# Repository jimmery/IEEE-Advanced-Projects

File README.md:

# IEEE-Advanced-Projects
Labs and Code for UCLA IEEE Advanced Projects.

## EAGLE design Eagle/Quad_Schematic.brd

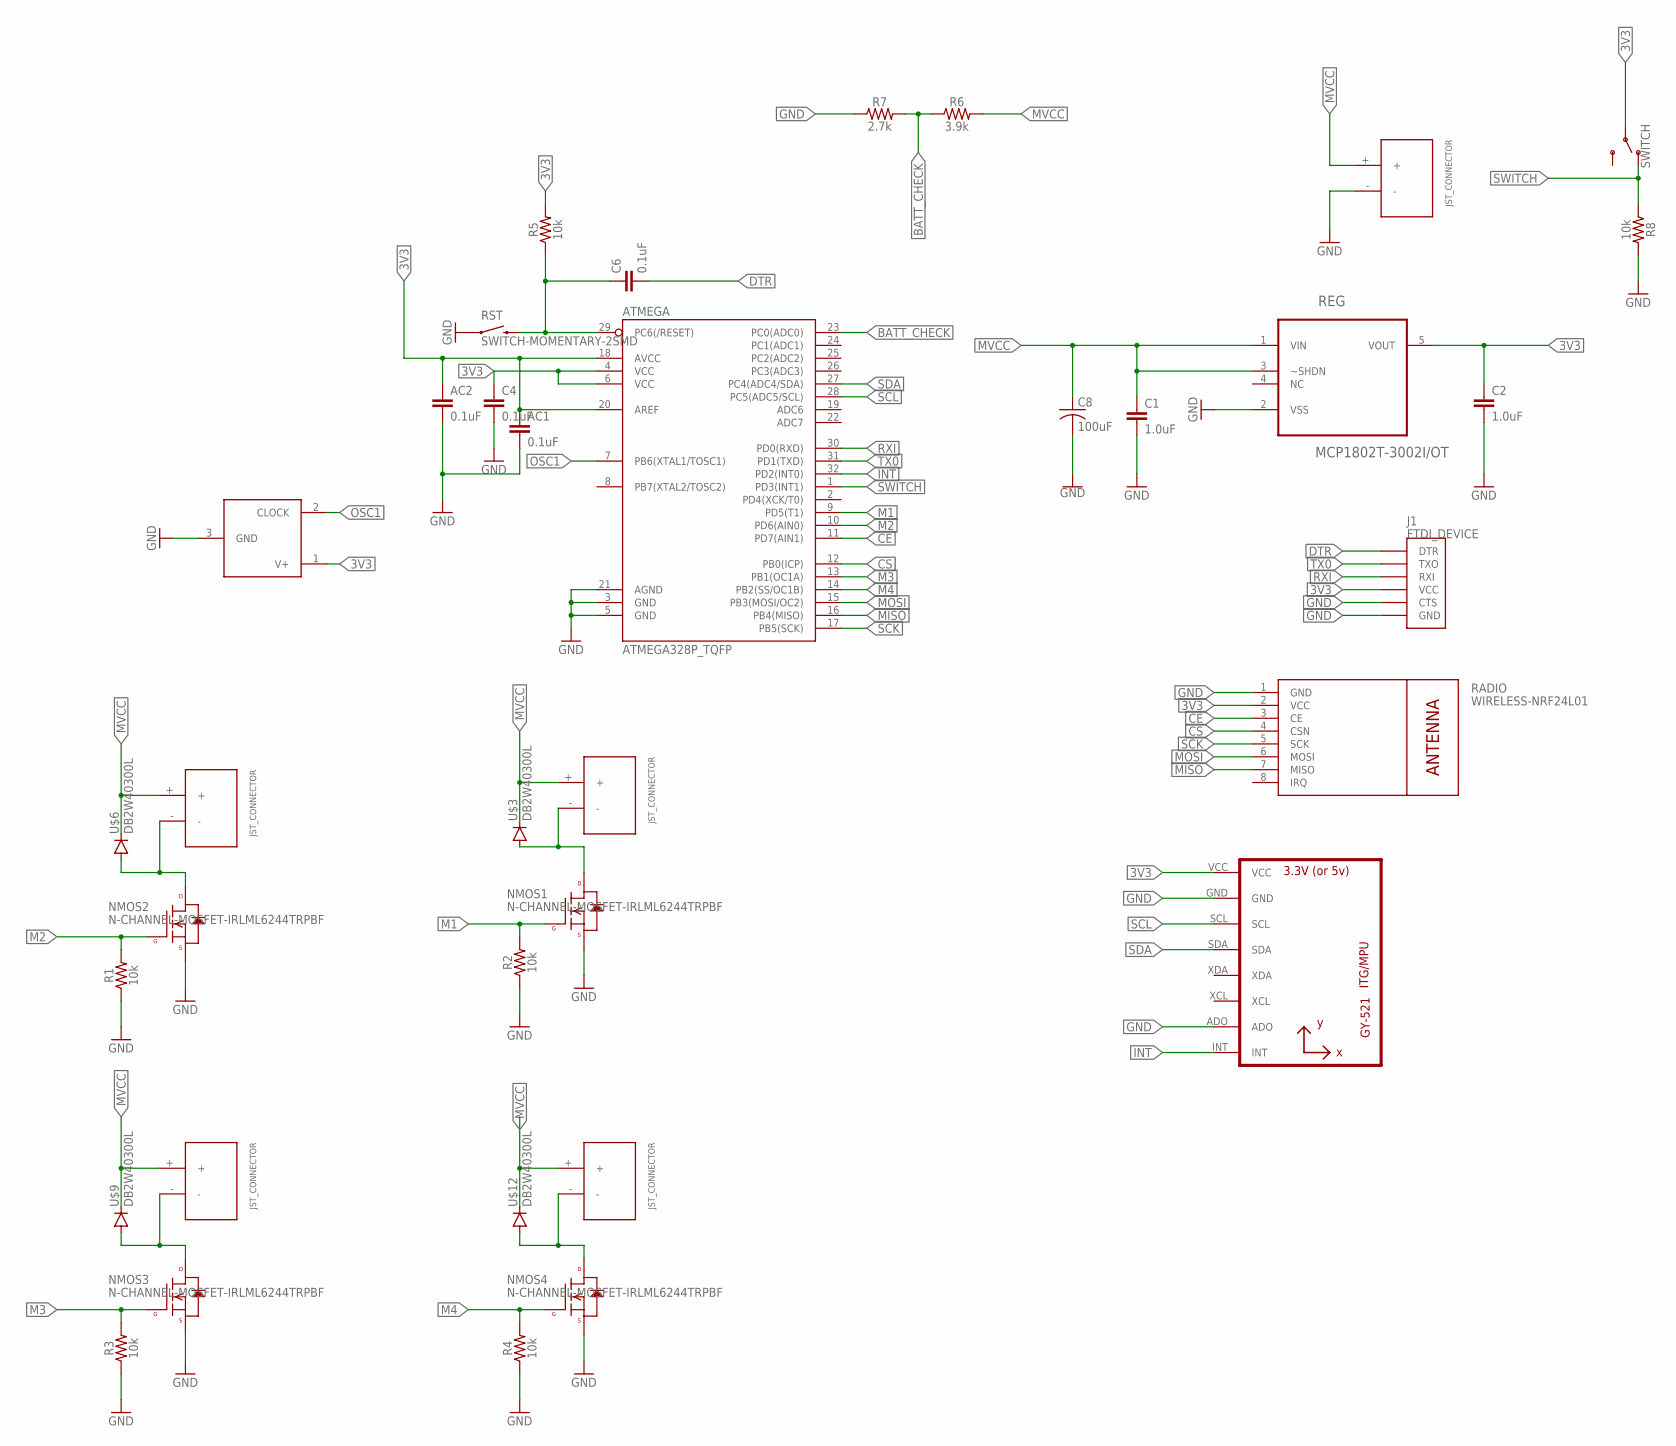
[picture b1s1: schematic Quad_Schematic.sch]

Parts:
AC1, AC2: 0.1uF; 0603
ATMEGA: ATMEGA328P_TQFP; TQFP32-08
BATT: JST_CONNECTOR_FEMALE
C1, C2: 1.0uF; 0603
C4, C6: 0.1uF; 0603
C8: 100uF; C1210
J1: FTDI_DEVICE; FTDI_DEVICE_SIDE
NMOS1, NMOS2, NMOS3, NMOS4: N-CHANNEL-MOSFET-IRLML6244TRPBF; SOT23-3
OSC: MAX7375; SC70-3L
R1, R2, R3, R4, R5, R8: 10k; 0603
R6: 3.9k; 0603
R7: 2.7k; 0603
RADIO: WIRELESS-NRF24L01
REG: MCP1802T-3002I/OT; SOT95P270X145-5N
RST: SWITCH-MOMENTARY-2SMD; TACTILE-SWITCH-SMD
SWITCH: SWITCH-SPDT-PTH-11.6X4.0MM; SWITCH_SPDT_PTH_11.6X4.0MM
U2: GY-521MPU6050; GY-521
U$2, U$5, U$8, U$11: JST_CONNECTOR_FEMALE
U$3, U$6, U$9, U$12: DB2W40300L; MINI2-F3-B

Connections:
3V3: AC1.1, AC2.1, ATMEGA.4 (VCC), ATMEGA.6 (VCC), ATMEGA.18 (AVCC), ATMEGA.20 (AREF), C2.1, C4.1, J1.P$4 (VCC), OSC.1 (V+), R5.2, RADIO.2 (VCC), REG.5 (VOUT), SWITCH.2, U2.VCC
BATT_CHECK: ATMEGA.23 (PC0(ADC0)), R6.1, R7.2
CE: ATMEGA.11 (PD7(AIN1)), RADIO.3 (CE)
CS: ATMEGA.12 (PB0(ICP)), RADIO.4 (CSN)
DTR: C6.2, J1.P$1 (DTR)
GND: AC1.2, AC2.2, ATMEGA.3 (GND), ATMEGA.5 (GND), ATMEGA.21 (AGND), BATT.-, C1.2, C2.2, C4.2, C8.2, J1.P$5 (CTS), J1.P$6 (GND), NMOS1.2 (S), NMOS2.2 (S), NMOS3.2 (S), NMOS4.2 (S), OSC.3 (GND), R1.1, R2.1, R3.1, R4.1, R7.1, R8.2, RADIO.1 (GND), REG.2 (VSS), RST.1, U2.ADO, U2.GND
INT: ATMEGA.32 (PD2(INT0)), U2.INT
M1: ATMEGA.9 (PD5(T1)), NMOS1.1 (G), R2.2
M2: ATMEGA.10 (PD6(AIN0)), NMOS2.1 (G), R1.2
M3: ATMEGA.13 (PB1(OC1A)), NMOS3.1 (G), R3.2
M4: ATMEGA.14 (PB2(SS/OC1B)), NMOS4.1 (G), R4.2
MISO: ATMEGA.16 (PB4(MISO)), RADIO.7 (MISO)
MOSI: ATMEGA.15 (PB3(MOSI/OC2)), RADIO.6 (MOSI)
MVCC: BATT.+, C1.1, C8.1, R6.2, REG.1 (VIN), REG.3 (~SHDN), U$2.+, U$3.NEG (GPIN), U$5.+, U$6.NEG (GPIN), U$8.+, U$9.NEG (GPIN), U$11.+, U$12.NEG (GPIN)
unnamed: NMOS1.3 (D), U$2.-, U$3.POS (PPIN)
unnamed: NMOS2.3 (D), U$5.-, U$6.POS (PPIN)
unnamed: NMOS4.3 (D), U$11.-, U$12.POS (PPIN)
unnamed: NMOS3.3 (D), U$8.-, U$9.POS (PPIN)
OSC1: ATMEGA.7 (PB6(XTAL1/TOSC1)), OSC.2 (CLOCK)
RESET: ATMEGA.29 (PC6(/RESET)), C6.1, R5.1, RST.3 (2)
RXI: ATMEGA.30 (PD0(RXD)), J1.P$3 (RXI)
SCK: ATMEGA.17 (PB5(SCK)), RADIO.5 (SCK)
SCL: ATMEGA.28 (PC5(ADC5/SCL)), U2.SCL
SDA: ATMEGA.27 (PC4(ADC4/SDA)), U2.SDA
SWITCH: ATMEGA.1 (PD3(INT1)), R8.1, SWITCH.1 (O)
TX0: ATMEGA.31 (PD1(TXD)), J1.P$2 (TXO)

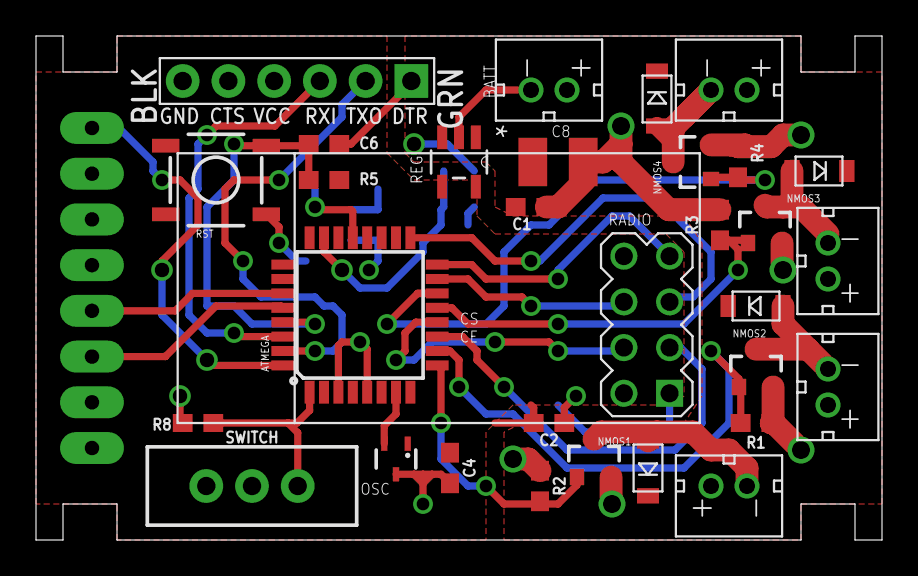
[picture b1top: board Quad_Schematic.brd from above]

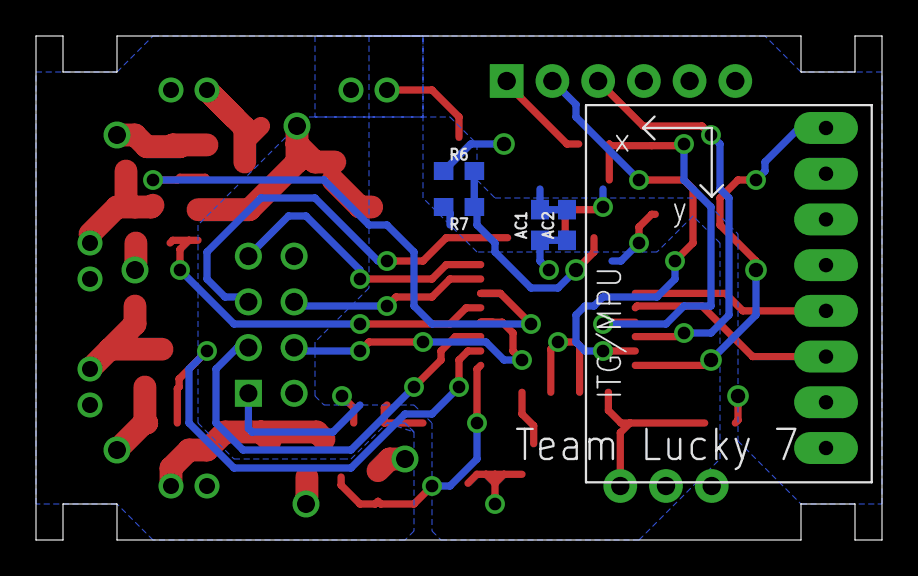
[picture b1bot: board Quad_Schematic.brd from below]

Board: 2 copper layers, 47.0 x 28.0 mm, 36 parts (5 on the bottom side), 26 nets.

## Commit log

2016-10-19 this is a slight change to the code that we 'submitted' to Cullen for this part. I added a couple of functions to further modularize the code. I plan on doing some significant changes after this comm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
2016-10-19 quick fix to the 'submission' code. what we had earlier was going to fail for sure. however, it's only a couple lines that i recommented out, that will change for the next part. this is simply a nice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
2016-10-19 I think I did it? We'll test it later, if it even matters for the next lab.
2016-11-03 moving files to other computer to test codes.
2016-11-03 Pin assignments
    Added
2016-11-03 it's not working. :( at least it's compiling.
2016-11-03 i don't know what's happening.
2016-11-03 Upload of nRF24L01.h and cleanup of RF24.cpp
    ^^
2016-11-05 update
    yes
2016-11-05 library files added
    here
2016-11-06 checkpoint B looks like it's done. we got printDetails working correctly.
2016-11-06 pin assignments updated
    also radio stuff
2016-11-06 struct added.
2016-11-08 added a new code for Arduino, because they will have different codes
    ok
2016-11-08 removed extra arduino file
    may be cause of problem
2016-11-08 cleanup (again)
    ok
2016-11-08 pre-C test
2016-11-08 finished C, trying to get space team working again.
2016-11-08 some comments that explain some stuff
    yeah
2016-11-08 fix buffer size stuff.
2016-11-10 hello world.
2016-11-10 added a println
    ya
2016-11-10 fix
    text
2016-11-10 comments
    lots of them
2016-11-10 Correct Teensy controller
2016-11-10 hopefully merge worked.
2016-11-14 the one less than thas is not less than or grater than or equal to
    literally the final fix
2016-11-14 working teensy space team code.
2016-11-15 the beginning of the airmouse
2016-11-17 universal data types
    yeah
2016-11-17 housekeeping
    notes
2016-11-18 apparently i changed pin assignments again
    lol
2016-11-18 added bat check, left, and right pinouts
    yeah
2016-11-18 working airmouse part 1
2016-11-18 working airmouse part 1 arduino
2016-11-29 added a quick functionality thing to allow for there to be a signal when a button is unpressed.
2016-11-29 added some IMU receiver stuff.
2016-11-29 comments
    yeh
2016-11-29 hopefully this is now able to send accelerometer + gyro data.
2016-11-29 took out printf related thigns
    ok
2016-11-29 hopefully again, this works.
2016-11-29 this one should actually work.
2016-11-29 took out printf
    yeah
2016-11-29 added comments to make sure that i can commit
    yaeh
2016-11-29 pushed changes to make sure clicks prin tout
2016-11-29 added print acceleration
2016-11-30 push
    spush
2016-11-30 what's working for me.
2016-11-30 hello world. we are done with airmouse.
2017-02-21 added layout stuff.
2017-02-22 placement and initial polygons added to layout
2017-02-22 tried implementing multiple grounds.
2017-02-22 kinda more optimized, but not a lot of traces done.
2017-02-22 re-organized
2017-02-22 23 airwires left
2017-03-01 the first submission
2017-03-01 2 airwires left
2017-03-02 moved batt_check
    also rip
2017-03-02 jeffrey approved this
2017-03-06 GOGOGO
    basically done?
2017-03-07 fixed naming and such

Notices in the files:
parts and their libraries:
SparkFun-Capacitors: Licensing: Creative Commons ShareAlike 4.0 International - https://creativecommons.org/licenses/by-sa/4.0
